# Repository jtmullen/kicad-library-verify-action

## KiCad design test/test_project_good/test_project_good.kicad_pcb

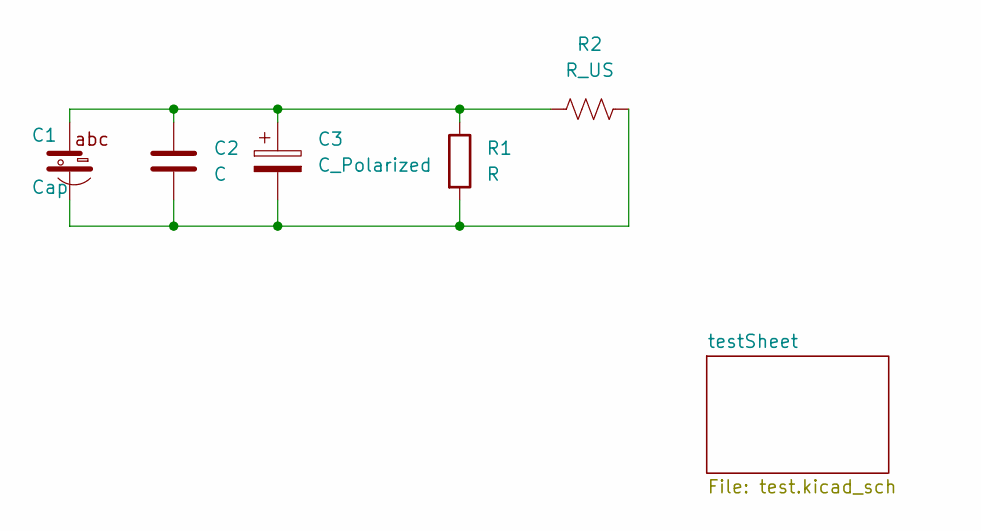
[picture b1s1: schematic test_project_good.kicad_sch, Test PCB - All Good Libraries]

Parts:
C1: Cap; C_0805_MOD
C2: C; C_2220_5650Metric_Pad1.97x5.40mm_HandSolder
C3: C_Polarized; CP_Elec_6.3x5.3
R1: R; R_0612_1632Metric_Pad1.18x3.40mm_HandSolder
R2: R_US; R_4020_10251Metric_Pad1.65x5.30mm_HandSolder

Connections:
unnamed: C1.1, C2.1, C3.1, R1.1, R2.1
unnamed: C1.2, C2.2, C3.2, R1.2, R2.2

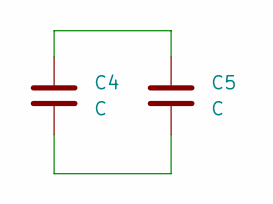
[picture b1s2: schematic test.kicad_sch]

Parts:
C4, C5: C; C_0603_1608Metric

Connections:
unnamed: C4.1, C5.1
unnamed: C4.2, C5.2

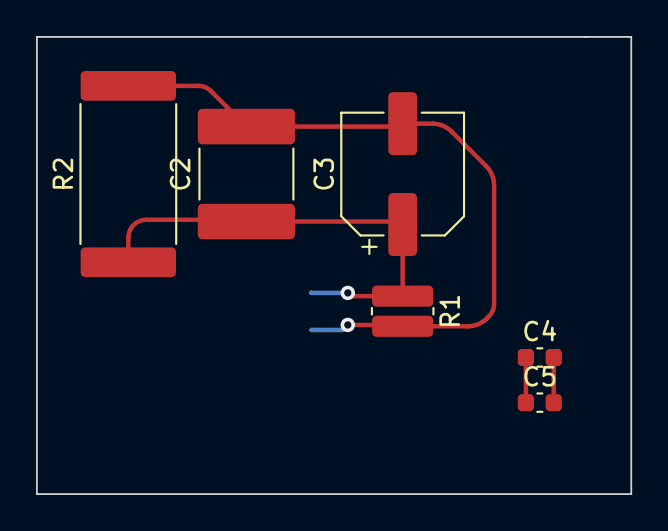
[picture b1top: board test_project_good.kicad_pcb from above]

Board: 2 copper layers, 33.0 x 25.4 mm, 7 parts (1 on the bottom side), 4 nets.

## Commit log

2022-04-13 Submodule added
2022-04-24 ignore for kicad
2022-04-24 Test files
2022-05-24 Symbol check working
2022-06-04 Github Actions testing
2022-06-04 Fix runner name
2022-06-04 Fix runner name actually
2022-06-04 Copy requirements
2022-06-04 reqs path
2022-06-04 Try path fix
2022-06-04 Do it directly
2022-06-04 Remove -r
2022-06-04 Change image
2022-06-04 rm unneeded git requirement
2022-06-04 Fix git install
2022-06-04 Fix path construction
2022-06-04 Output and improved logging:
2022-06-04 Fix typo
2022-06-04 Improved logging more
2022-06-04 Cont on error
2022-06-04 Debug logs
2022-06-04 re order correctly
2022-06-04 Re-order more
2022-06-04 Addl. Test
2022-06-04 Fix relative paths
2022-06-04 Fix broken print
2022-06-04 log -> info
2022-06-04 Fix test command
2022-06-04 Fix test command round 3
2022-06-04 Sort fails for consistent output
2022-06-04 Fix sorting
2022-06-04 Syntax error fix
2022-06-04 Fix matching quotes'
2022-08-18 Support for only changed files
2022-08-20 Fix dockerfile
2022-08-20 Python syntax
2022-08-22 Boolean input
2022-08-22 Import JSON
2022-09-01 Verify sym library file extension
2022-09-01 handle varibale len pad definition
2022-09-01 fix indexing
2022-09-01 syntax fix
2022-09-01 Fix last reference to item[4][3]
